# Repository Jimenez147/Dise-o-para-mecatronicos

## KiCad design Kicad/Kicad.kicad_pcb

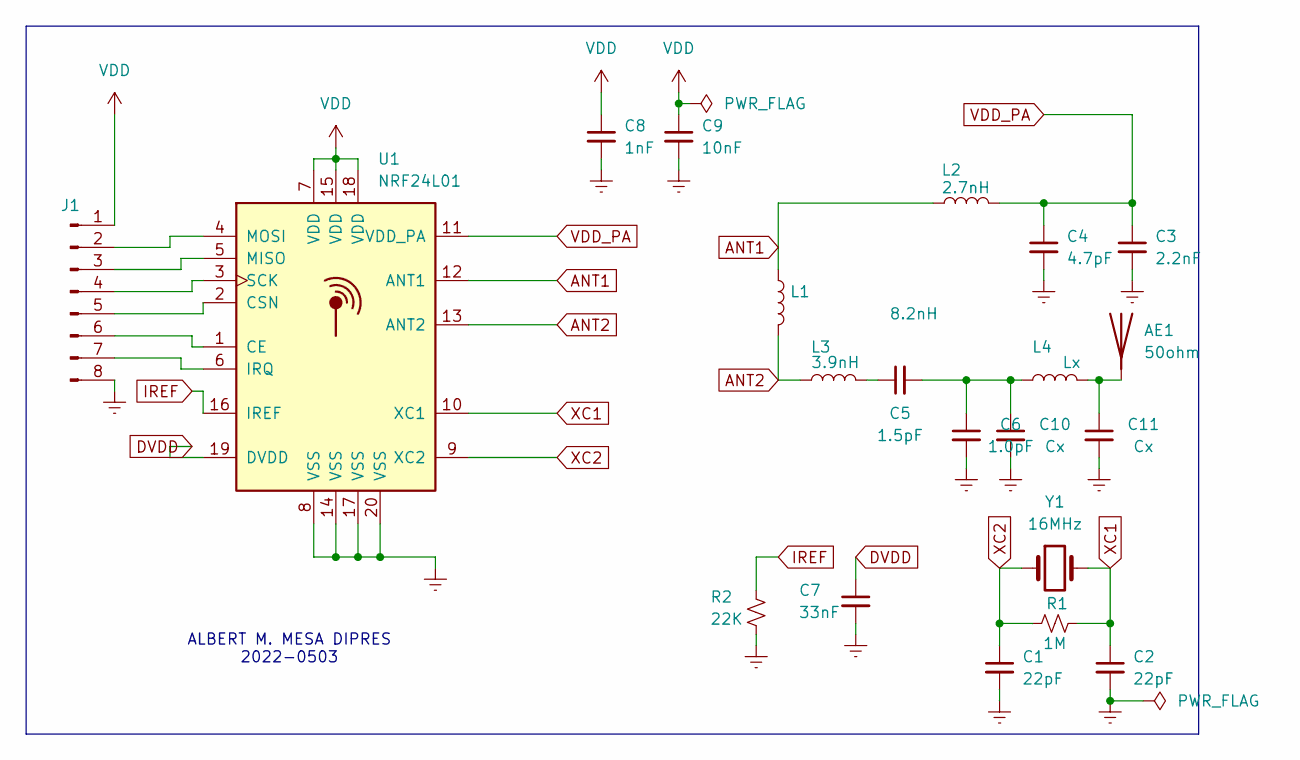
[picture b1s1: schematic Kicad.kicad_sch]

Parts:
AE1: 50ohm; Texas_SWRA117D_2.4GHz_Right
C1, C2: 22pF; C_0402_1005Metric
C3: 2.2nF; C_0402_1005Metric
C4: 4.7pF; C_0402_1005Metric
C5: 1.5pF; C_0402_1005Metric
C6: 1.0pF; C_0402_1005Metric
C7: 33nF; C_0402_1005Metric
C8: 1nF; C_0402_1005Metric
C9: 10nF; C_0402_1005Metric
C10, C11: Cx; C_0402_1005Metric
J1: Conn_01x08_Pin; Hirose_DF13-08P-1.25DSA_1x08_P1.25mm_Vertical
L1: 8.2nH; L_0402_1005Metric
L2: 2.7nH; L_0402_1005Metric
L3: 3.9nH; L_0402_1005Metric
L4: Lx; L_0402_1005Metric
R1: 1M; R_0402_1005Metric
R2: 22K; R_0402_1005Metric
U1: NRF24L01; QFN-20-1EP_4x4mm_P0.5mm_EP2.5x2.5mm
Y1: 16MHz; Crystal_SMD_3215-2Pin_3.2x1.5mm

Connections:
GNDREF: C1.2, C2.2, C3.2, C4.2, C6.2, C7.2, C8.2, C9.2, C10.2, C11.2, J1.8, R2.2, U1.8 (VSS), U1.14 (VSS), U1.17 (VSS), U1.20 (VSS)
unnamed: AE1.1 (A), C11.1, L4.2
unnamed: C5.1, L3.2
unnamed: C5.2, C6.1, C10.1, L4.1
unnamed: J1.2, U1.4 (MOSI)
unnamed: J1.3, U1.5 (MISO)
unnamed: J1.4, U1.3 (SCK)
unnamed: J1.5, U1.2 (CSN)
unnamed: J1.6, U1.1 (CE)
unnamed: J1.7, U1.6 (IRQ)
unnamed: L1.1, L2.1, U1.12 (ANT1)
unnamed: L1.2, L3.1, U1.13 (ANT2)
unnamed: C7.1, U1.19 (DVDD)
unnamed: R2.1, U1.16 (IREF)
unnamed: C3.1, C4.1, L2.2, U1.11 (VDD_PA)
unnamed: C2.1, R1.2, U1.10 (XC1), Y1.2
unnamed: C1.1, R1.1, U1.9 (XC2), Y1.1
VDD: C8.1, C9.1, J1.1, U1.7 (VDD), U1.15 (VDD), U1.18 (VDD)

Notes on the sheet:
ALBERT M. MESA DIPRES 2022-0503

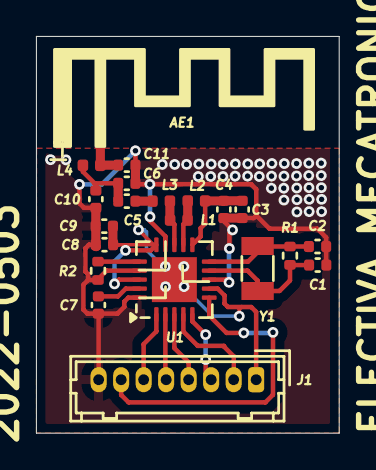
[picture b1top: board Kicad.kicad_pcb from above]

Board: 2 copper layers, 16.8 x 22.0 mm, 21 parts (0 on the bottom side), 18 nets.

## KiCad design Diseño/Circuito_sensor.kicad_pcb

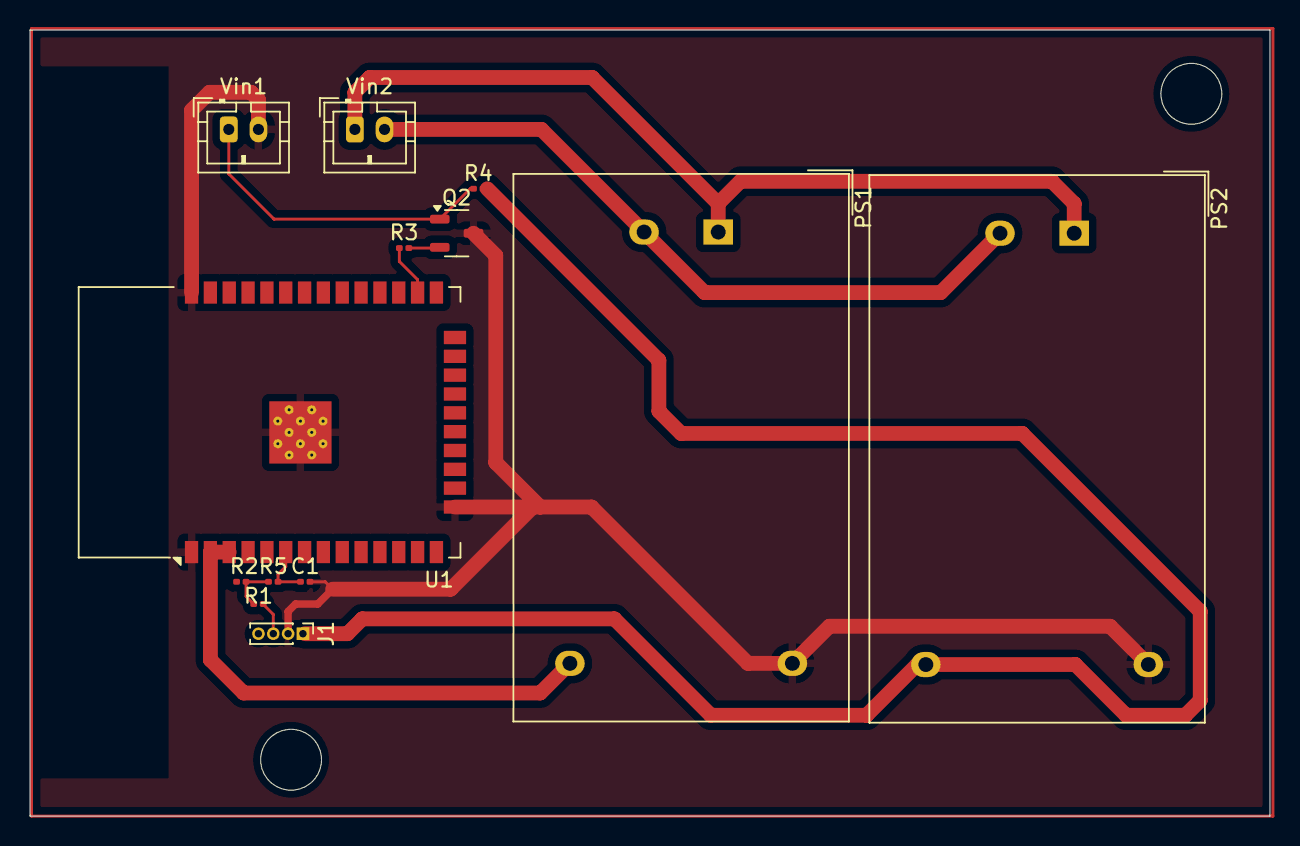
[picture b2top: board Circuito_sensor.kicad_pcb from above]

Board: 2 copper layers, 83.6 x 53.0 mm, 13 parts (0 on the bottom side), 11 nets.

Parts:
C1: C; C_0201_0603Metric
J1: Sensor; PinHeader_1x04_P1.00mm_Vertical
PS1: HLK-PM03; Converter_ACDC_Hi-Link_HLK-PMxx
PS2: HLK-PM01; Converter_ACDC_Hi-Link_HLK-PMxx
Q2: MMBTH10-4LT1G; SOT-23-3
R1, R2, R3, R4, R5: R; R_0201_0603Metric
U1: ESP32-WROOM-32
Vin1: Buzzer; JST_PH_B2B-PH-K_1x02_P2.00mm_Vertical
Vin2: Conn_01x02_Pin; JST_PH_B2B-PH-K_1x02_P2.00mm_Vertical

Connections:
+3.3V: PS1.4 (+Vout), U1.2 (VDD), U1.3 (EN)
+5V: J1.1, PS2.4 (+Vout), R4.2
/ADC: C1.1, R5.2, U1.6 (IO34)
/En: R3.1, U1.26 (IO4)
GND: C1.2, J1.2, PS1.3 (-Vout), PS2.3 (-Vout), Q2.3 (E), R2.1, U1.1 (GND), U1.15 (GND), U1.38 (GND), U1.39 (GND), Vin1.2
unnamed: J1.3, R1.2
unnamed: PS1.1 (AC/L), PS2.1 (AC/L), Vin2.1
unnamed: PS1.2 (AC/N), PS2.2 (AC/N), Vin2.2
unnamed: Q2.2 (B), R3.2
unnamed: Q2.1 (C), R4.1, Vin1.1
unnamed: R1.1, R2.2, R5.1

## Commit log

2024-09-13 Clase 1
2024-10-03 CAD y Documentacion
2024-10-18 18/10
2024-11-29 Actualizacion
2024-12-06 Circuito
